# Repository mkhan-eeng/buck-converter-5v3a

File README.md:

# buck-converter-5v3a
First-principles design of a 12V to 5V 3A asynchronous buck converter (TI TPS54360);  full calculations, Type II loop compensation, and 4-layer KiCad PCB.
# 12V to 5V 3A Synchronous Buck Converter

A complete design of a non-isolated step-down DC-DC converter producing a
regulated 5V/3A output from a 12V input, built around the TI TPS54360.
Designed from first principles in KiCad, with full calculations, control-loop
compensation, and a 4-layer PCB layout.

## Specifications
| Parameter | Value |
|-----------|-------|
| Input | 10.8–13.2V (12V nominal) |
| Output | 5V ±2%, 0–3A |
| Ripple | <50mV pp |
| Switching frequency | 500 kHz |
| Topology | Asynchronous buck (HS FET + Schottky) |
| Predicted efficiency | 89.7% at full load |
| Phase margin | ~62° |

## Highlights
- Every component value derived from first principles (TPS54360 datasheet
  equations + worst-case operating-point analysis)
- Type II compensator designed for ~50 kHz crossover, verified by Python
  Bode analysis and an independent hand calculation
- 4-layer PCB with tight switching loop, internal ground plane, and thermal
  vias under the controller and Schottky
- ERC clean, DRC clean

## Repository structure
- `report/` — full design report (PDF)
- `calculations/` — LaTeX calculations and Python analysis scripts
- `kicad/` — KiCad project, schematic, and PCB files
- `images/` — schematic, PCB, and 3D renders
- `gerbers/` — fabrication output

## Tools
KiCad 9, Python (NumPy/SciPy/matplotlib), LaTeX

## Status
Complete paper design verified by analysis. Prototype build and bench
validation planned as next step.

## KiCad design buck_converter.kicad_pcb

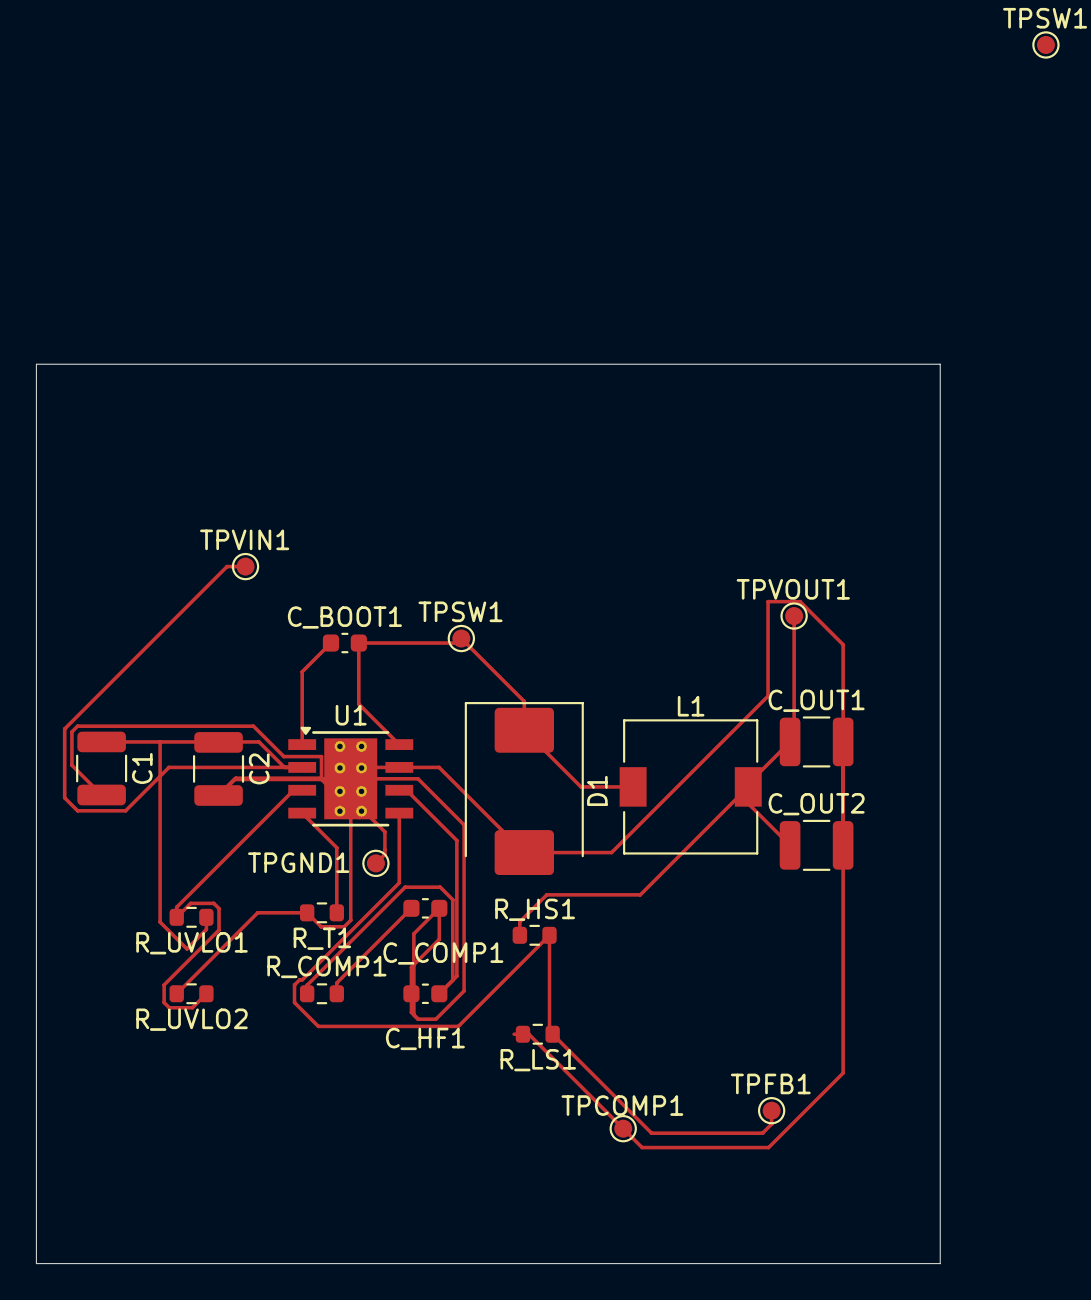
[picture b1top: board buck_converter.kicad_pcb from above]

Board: 4 copper layers, 50.2 x 50.0 mm, 23 parts (0 on the bottom side), 10 nets.

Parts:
C1, C2: 4.7µ; C_1210_3225Metric
C_BOOT1: 100nF; C_0603_1608Metric
C_COMP1: 3.3n; C_0603_1608Metric
C_HF1: 22p; C_0603_1608Metric
C_OUT1, C_OUT2: 47µ; C_1210_3225Metric
D1: B560C; D_SMC
L1: 8.2µ; L_7.3x7.3_H4.5
R_COMP1: 30.9k; R_0603_1608Metric
R_HS1: 52.3k; R_0603_1608Metric
R_LS1: 10.0k; R_0603_1608Metric
R_T1: 191k; R_0603_1608Metric
R_UVLO1: 294k; R_0603_1608Metric
R_UVLO2: 43.2k; R_0603_1608Metric
TPCOMP1: TestPoint; TestPoint_Pad_D1.0mm
TPFB1: TestPoint; TestPoint_Pad_D1.0mm
TPGND1: TestPoint; TestPoint_Pad_D1.0mm
TPSW1, TPSW1#2: TestPoint; TestPoint_Pad_D1.0mm
TPVIN1: TestPoint; TestPoint_Pad_D1.0mm
TPVOUT1: TestPoint; TestPoint_Pad_D1.0mm
U1: TPS54360DDA; TI_SO-PowerPAD-8_ThermalVias

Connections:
/VIN: C1.1, C2.1, R_UVLO1.1, TPVIN1.1, U1.2 (VIN)
/VOUT: C_OUT1.1, C_OUT2.1, L1.2, R_HS1.1, TPVOUT1.1
GNDREF: C1.2, C2.2, C_COMP1.2, C_HF1.2, C_OUT1.2, C_OUT2.2, D1.2 (A), R_LS1.2, R_T1.2, R_UVLO2.2, TPCOMP1.1, TPGND1.1, U1.7 (GND), U1.9 (GNDPAD)
unnamed: C_COMP1.1, R_COMP1.2
unnamed: C_BOOT1.2, D1.1 (K), L1.1, TPSW1#2.1, U1.8 (SW)
unnamed: C_BOOT1.1, U1.1 (BOOT)
unnamed: C_HF1.1, R_COMP1.1, U1.6 (COMP)
unnamed: R_UVLO1.2, R_UVLO2.1, U1.3 (EN)
unnamed: R_HS1.2, R_LS1.1, TPFB1.1, U1.5 (FB)
unnamed: R_T1.1, U1.4 (RT/CLK)
